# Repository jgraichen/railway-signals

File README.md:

# German model railway signals

<em lang="en">This repository contains 3d models, parts, and electronic components and boards to build german railway signals for H0 model railroading.</em>

## Signalkomponenten

- [Masten, Körbe, Zubehör](freecad/KS/Masten/README.md)
- [KS-Signalschirme](freecad/KS/Signalschirme/README.md)
  - [PCB für Hauptsignale](kicad/Hauptsignal/README.md)
  - [PCB für Mehrabschnittssignale](kicad/Mehrabschnittssignal/README.md)
  - [PCB für Vorsignale](kicad/Vorsignal/README.md)
- [Zusatzsignale](freecad/KS/Zusatzsignale/README.md)
  - [PCB für Zusatzsignale](kicad/Zusatzsignal/README.md)

## Zubehör

### Signal-Treiberplatinen

- [Adapterplatine für MGP Signaldekoder](kicad/extra/ws2811-adapter/README.md)
- [LED Treiberboard für ein wechselbares Lichtsperrsignal](kicad/extra/ws2811-driver-6ls/README.md)
- [LED Treiberboard für zwei wechselbare Lichtsperrsignale](kicad/extra/ws2811-driver-9ls/README.md)
- [12 LED Treiberboard (1 Signal)](kicad/extra/ws2811-driver-12/README.md)
- [24 LED Treiberboard (2 Signale)](kicad/extra/ws2811-driver-24/README.md)
- [Wattenscheider Schacht für LED Treiberboards](freecad/watti-signal-mount/README.md)

## License

See individual components. Otherwise, all components and parts are licensed under a [Creative Commons Attribution-ShareAlike 4.0 International License](http://creativecommons.org/licenses/by-sa/4.0/).

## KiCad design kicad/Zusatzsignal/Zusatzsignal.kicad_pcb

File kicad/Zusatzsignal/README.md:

# Zusatzsignal ZSv2

Geeignet für Zusatzsignale über oder unter dem Signalschirm.

## Anschlussbelegung

| Referenz | Pin | LED | Funktion            |
| -------- | --- | --- | ------------------- |
|          | +   |     | Stromversorgung (+) |
|          |     |     | Masse               |

## License

This work is licensed under a
[Creative Commons Attribution-ShareAlike 4.0 International License](http://creativecommons.org/licenses/by-sa/4.0/).

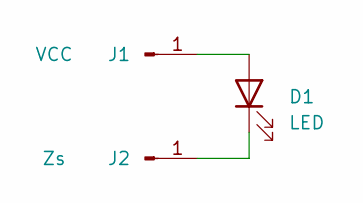
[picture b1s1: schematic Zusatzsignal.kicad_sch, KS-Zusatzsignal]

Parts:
D1: LED; LED_0603_1608Metric
J1: VCC; SolderWirePad_1x01_SMD_1x2mm
J2: Zs; SolderWirePad_1x01_SMD_1x2mm

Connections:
unnamed: D1.1 (K), J2.1
unnamed: D1.2 (A), J1.1

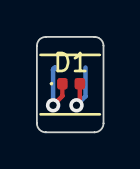
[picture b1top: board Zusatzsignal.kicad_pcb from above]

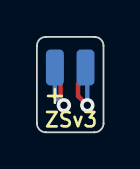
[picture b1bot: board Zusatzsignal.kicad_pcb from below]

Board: 2 copper layers, 3.7 x 5.3 mm, 3 parts (2 on the bottom side), 2 nets.

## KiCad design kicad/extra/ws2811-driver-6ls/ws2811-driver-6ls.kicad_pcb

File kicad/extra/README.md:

# Extra components

## WS2811 Adapter Board

An adapter boards to connect MGP signal decoders with driver boards via RJ45 cables, for longer distances and easier cabling.

Supports bypassing ports and looping back the digital signal to organize and optimize LED ordering. See the [board README](ws2811-adapter/README.md) for more details.

## WS2811 Driver 12 (1 Signal)

[LED driver board providing 12 LEDs](ws2811-driver-12/), intended for up to one fully equipped German KS signal. Can be mounted in a [Wattenscheider Schacht](../../freecad/watti-signal-mount/).

## WS2811 Driver 24 (2 Signals)

A [24 LED driver board](ws2811-driver-24/) for up to two fully equipped German KS signal, usually mounted on a signal gantry. Can be mounted in a [Wattenscheider Schacht](../../freecad/watti-signal-mount/).

## WS2811 Driver 6LS (1 LS)

This [driver board](ws2811-driver-6ls/) offers one tiny 2x3p 1 mm pitch connector for light shunting signals. The board can be mounted below the track, with the signal being mounted and connected through a 5 mm brass pole.

## WS2811 Driver 9LS (2 LS)

This [driver board](ws2811-driver-9ls/) offers two tiny 2x3p 1 mm pitch connectors for light shunting signals. The board can be mounted below the track, with the signal being mounted and connected through a 5 mm brass pole.

## License

See individual components. Otherwise, all components and parts are licensed under a [Creative Commons Attribution-ShareAlike 4.0 International License](http://creativecommons.org/licenses/by-sa/4.0/).

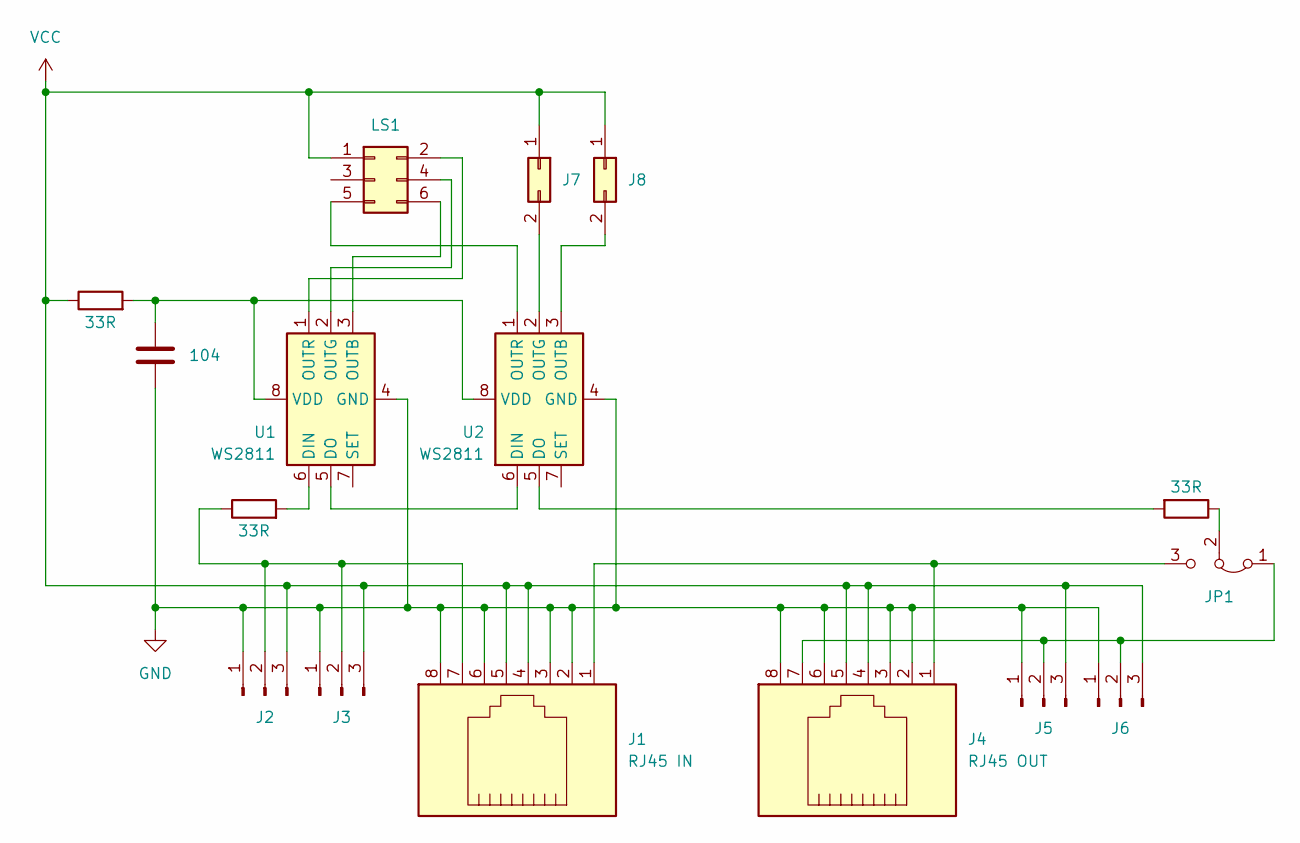
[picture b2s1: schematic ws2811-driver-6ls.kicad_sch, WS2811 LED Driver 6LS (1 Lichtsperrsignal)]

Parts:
C1: 104; C_0603_1608Metric; LCSC C14663
J1: RJ45 IN; RJ45_Amphenol_54602-x08_Horizontal
J2, J5: Conn_01x03_Pin; PinHeader_1x03_P2.54mm_Vertical
J3, J6: Conn_01x03_Pin; SolderWire-0.15sqmm_1x03_P4mm_D0.5mm_OD1.5mm_Relief
J4: RJ45 OUT; RJ45_Amphenol_54602-x08_Horizontal
J7, J8: Conn_02x01; PinHeader_2x01_P1.27mm_Vertical
JP1: Jumper_3_Bridged12; PinHeader_1x03_P2.54mm_Vertical
LS1: Conn_02x03_Odd_Even; PinHeader_2x03_P1.27mm_Vertical
R1, R2, R3: 33R; R_0603_1608Metric; LCSC C23140
U1, U2: WS2811; SOIC-8_3.9x4.9mm_P1.27mm; LCSC C114581

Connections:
GND: C1.2, J1.2, J1.3, J1.6, J1.8, J2.1, J3.1, J4.2, J4.3, J4.6, J4.8, J5.1, J6.1, U1.4 (GND), U2.4 (GND)
unnamed: J1.7, J2.2, J3.2, R2.1
unnamed: J4.7, J5.2, J6.2, JP1.1 (A)
unnamed: J7.2, U2.2 (OUTG)
unnamed: J8.2, U2.3 (OUTB)
unnamed: J1.1, J4.1, JP1.3 (B)
unnamed: JP1.2 (C), R3.1
unnamed: LS1.2, U1.1 (OUTR)
unnamed: LS1.4, U1.2 (OUTG)
unnamed: LS1.5, U2.1 (OUTR)
unnamed: LS1.6, U1.3 (OUTB)
unnamed: R2.2, U1.6 (DIN)
unnamed: U1.5 (DO), U2.6 (DIN)
unnamed: C1.1, R1.2, U1.8 (VDD), U2.8 (VDD)
unnamed: R3.2, U2.5 (DO)
VCC: J1.4, J1.5, J2.3, J3.3, J4.4, J4.5, J5.3, J6.3, J7.1, J8.1, LS1.1, R1.1

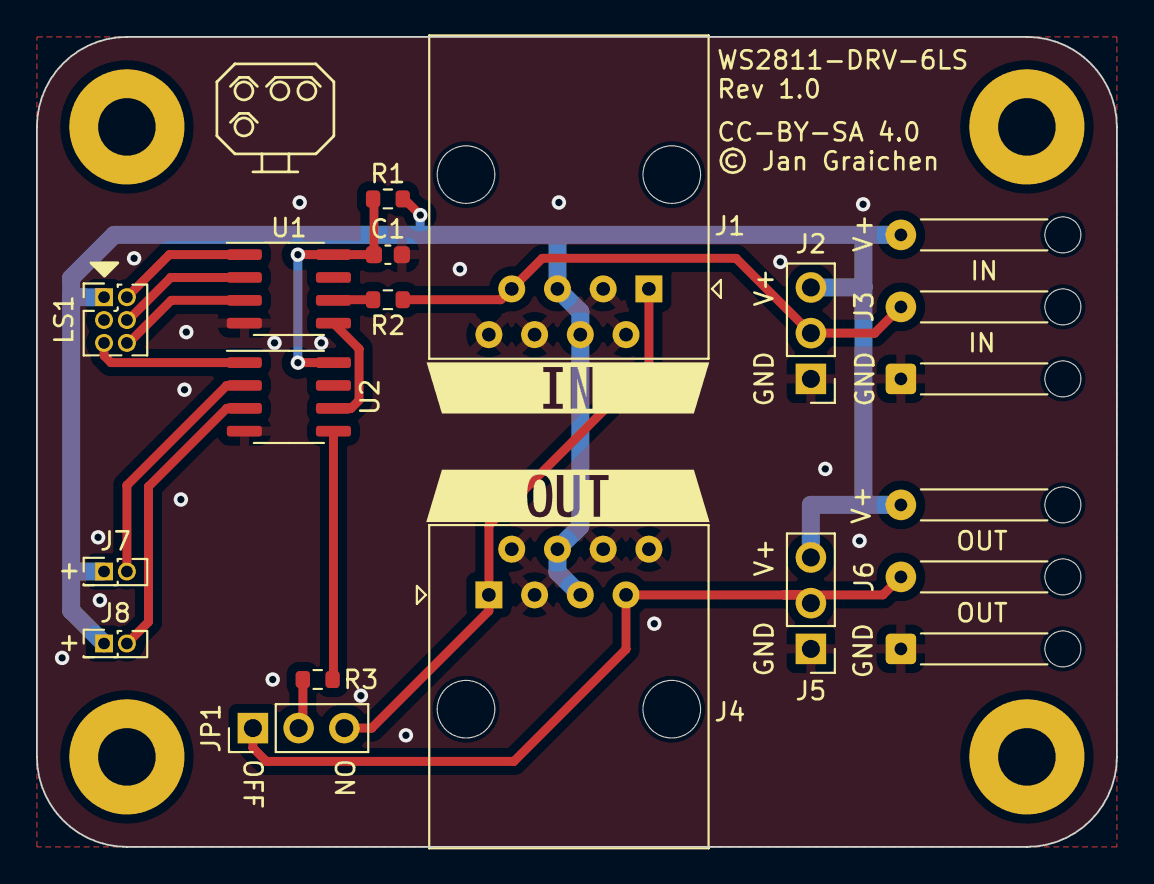
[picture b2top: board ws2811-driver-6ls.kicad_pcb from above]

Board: 2 copper layers, 60.0 x 45.0 mm, 18 parts (0 on the bottom side), 16 nets.

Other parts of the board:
kibuzzard-65AE6F8F: G***; kibuzzard-65AE6F8F
kibuzzard-65AE6F95: G***; kibuzzard-65AE6F95

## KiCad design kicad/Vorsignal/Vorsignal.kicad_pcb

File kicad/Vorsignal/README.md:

# Vorsignal

Geeignet für KS-Vorsignale.

## Anschlussbelegung

| Schema                | Pin-Belegung                    |
| --------------------- | ------------------------------- |
|  |  |

| Referenz | Pin | LED      | Funktion                   |
| -------- | --- | -------- | -------------------------- |
| J0       | +   |          | Stromversorgung (+)        |
| J1       | 1   | Kaltweiß | Verkürzter Bremswegabstand |
| J3       | 3   | Gelb     | Ks2 (Halt erwarten)        |
| J4       | 4   | Grün     | Ks1 (Fahrt erwarten)       |
| J9       | 9   | Kaltweiß | Wiederholer                |

## License

This work is licensed under a
[Creative Commons Attribution-ShareAlike 4.0 International License](http://creativecommons.org/licenses/by-sa/4.0/).

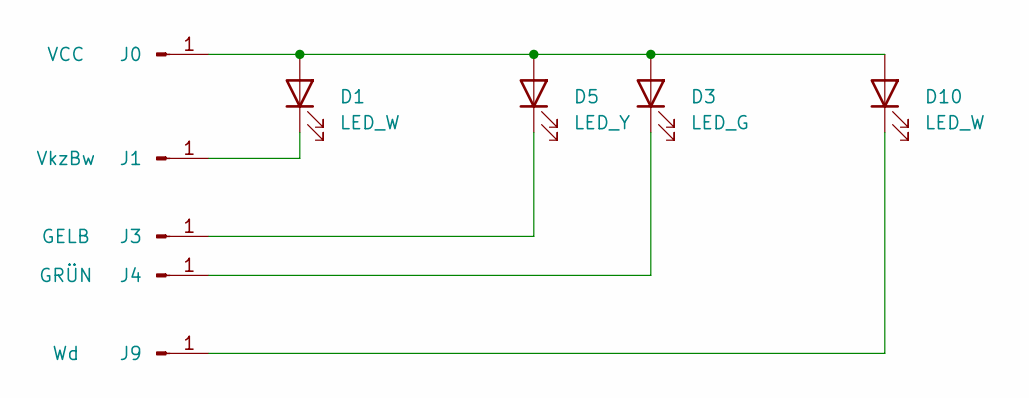
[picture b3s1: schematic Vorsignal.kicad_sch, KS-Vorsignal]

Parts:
D1, D10: LED_W; LED_0402_1005Metric; LCSC C189305
D3: LED_G; LED_0402_1005Metric; LCSC C409787
D5: LED_Y; LED_0402_1005Metric; LCSC C779450
J0: VCC; SolderWirePad_1x01_SMD_1x2mm
J1: VkzBw; SolderWirePad_1x01_SMD_1x2mm
J3: GELB; SolderWirePad_1x01_SMD_1x2mm
J4: GRÜN; SolderWirePad_1x01_SMD_1x2mm
J9: Wd; SolderWirePad_1x01_SMD_1x2mm

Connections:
unnamed: D1.2 (A), D3.2 (A), D5.2 (A), D10.2 (A), J0.1
unnamed: D1.1 (K), J1.1
unnamed: D3.1 (K), J4.1
unnamed: D5.1 (K), J3.1
unnamed: D10.1 (K), J9.1

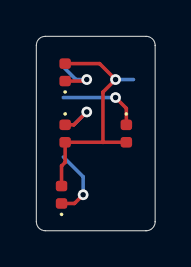
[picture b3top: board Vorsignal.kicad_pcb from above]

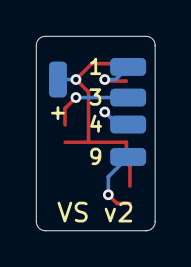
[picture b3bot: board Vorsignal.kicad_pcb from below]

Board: 2 copper layers, 6.6 x 10.8 mm, 9 parts (5 on the bottom side), 5 nets.

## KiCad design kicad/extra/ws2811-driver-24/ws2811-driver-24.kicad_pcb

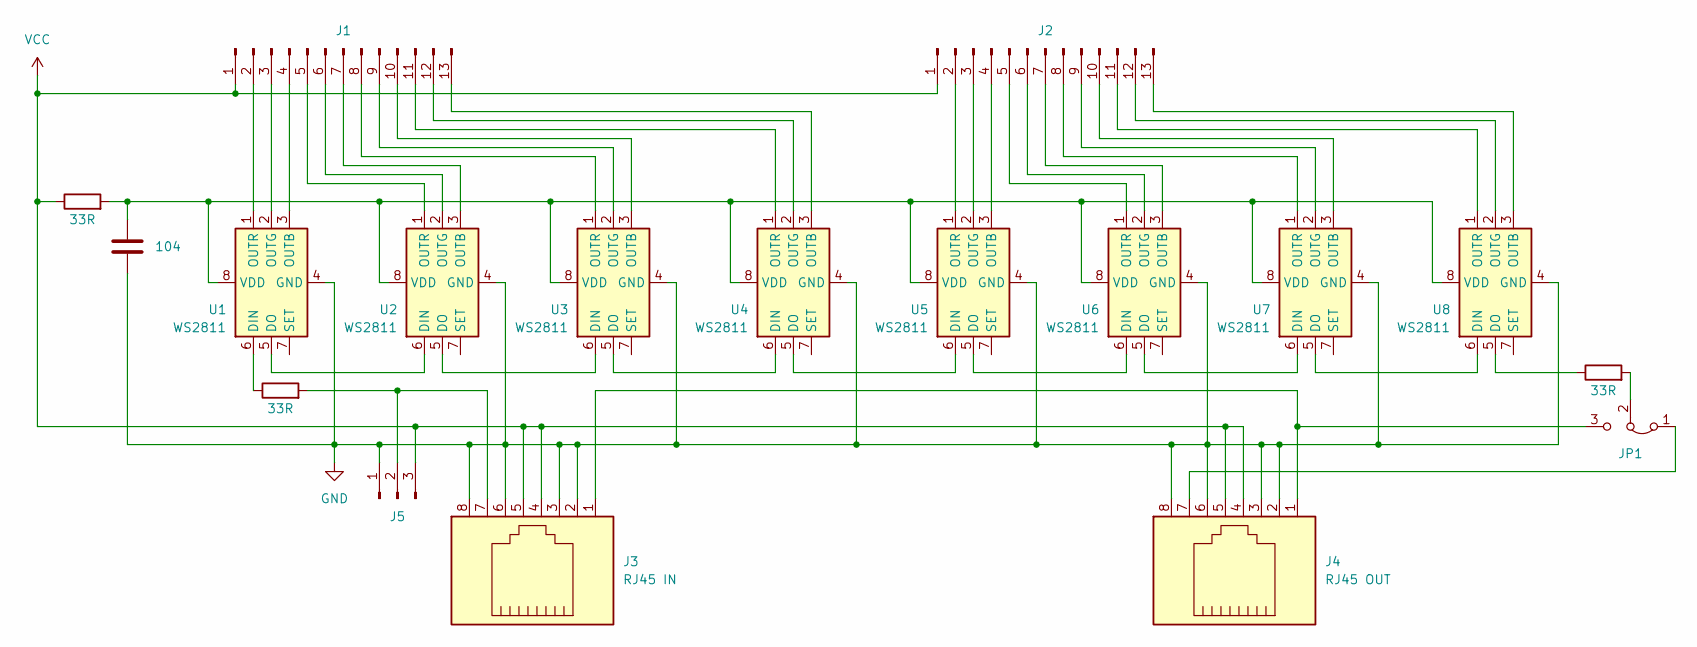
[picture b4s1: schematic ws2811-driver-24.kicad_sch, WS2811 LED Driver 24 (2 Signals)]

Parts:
C1: 104; C_0603_1608Metric
J1, J2: Conn_01x13_Pin; PinHeader_1x13_P2.54mm_Vertical
J3: RJ45 IN; RJ45_Amphenol_54602-x08_Horizontal
J4: RJ45 OUT; RJ45_Amphenol_54602-x08_Horizontal
J5: Conn_01x03_Pin; PinHeader_1x03_P2.54mm_Vertical
JP1: Jumper_3_Bridged12; PinHeader_1x03_P2.54mm_Vertical
R1, R2, R3: 33R; R_0603_1608Metric
U1, U2, U3, U4, U5, U6, U7, U8: WS2811; SOIC-8_3.9x4.9mm_P1.27mm

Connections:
GND: C1.2, J3.2, J3.3, J3.6, J3.8, J4.2, J4.3, J4.6, J4.8, J5.1, U1.4 (GND), U2.4 (GND), U3.4 (GND), U4.4 (GND), U5.4 (GND), U6.4 (GND), U7.4 (GND), U8.4 (GND)
unnamed: J1.2, U1.1 (OUTR)
unnamed: J1.3, U1.2 (OUTG)
unnamed: J1.4, U1.3 (OUTB)
unnamed: J1.5, U2.1 (OUTR)
unnamed: J1.6, U2.2 (OUTG)
unnamed: J1.7, U2.3 (OUTB)
unnamed: J1.8, U3.1 (OUTR)
unnamed: J1.9, U3.2 (OUTG)
unnamed: J1.10, U3.3 (OUTB)
unnamed: J1.11, U4.1 (OUTR)
unnamed: J1.12, U4.2 (OUTG)
unnamed: J1.13, U4.3 (OUTB)
unnamed: J2.2, U5.1 (OUTR)
unnamed: J2.3, U5.2 (OUTG)
unnamed: J2.4, U5.3 (OUTB)
unnamed: J2.5, U6.1 (OUTR)
unnamed: J2.6, U6.2 (OUTG)
unnamed: J2.7, U6.3 (OUTB)
unnamed: J2.8, U7.1 (OUTR)
unnamed: J2.9, U7.2 (OUTG)
unnamed: J2.10, U7.3 (OUTB)
unnamed: J2.11, U8.1 (OUTR)
unnamed: J2.12, U8.2 (OUTG)
unnamed: J2.13, U8.3 (OUTB)
unnamed: J3.7, J5.2, R2.2
unnamed: J4.7, JP1.1 (A)
unnamed: J3.1, J4.1, JP1.3 (B)
unnamed: JP1.2 (C), R3.2
unnamed: R2.1, U1.6 (DIN)
unnamed: U1.5 (DO), U2.6 (DIN)
unnamed: C1.1, R1.2, U1.8 (VDD), U2.8 (VDD), U3.8 (VDD), U4.8 (VDD), U5.8 (VDD), U6.8 (VDD), U7.8 (VDD), U8.8 (VDD)
unnamed: U2.5 (DO), U3.6 (DIN)
unnamed: U3.5 (DO), U4.6 (DIN)
unnamed: U4.5 (DO), U5.6 (DIN)
unnamed: U5.5 (DO), U6.6 (DIN)
unnamed: U6.5 (DO), U7.6 (DIN)
unnamed: U7.5 (DO), U8.6 (DIN)
unnamed: R3.1, U8.5 (DO)
VCC: J1.1, J2.1, J3.4, J3.5, J4.4, J4.5, J5.3, R1.1

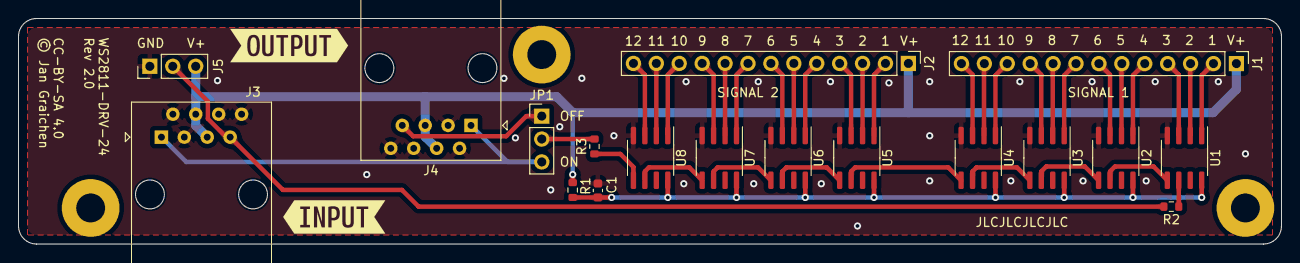
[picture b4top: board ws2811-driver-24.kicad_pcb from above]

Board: 2 copper layers, 140.0 x 25.0 mm, 20 parts (0 on the bottom side), 40 nets.

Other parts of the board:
kibuzzard-6563A51A: G***; kibuzzard-6563A51A
kibuzzard-6563A507: G***; kibuzzard-6563A507

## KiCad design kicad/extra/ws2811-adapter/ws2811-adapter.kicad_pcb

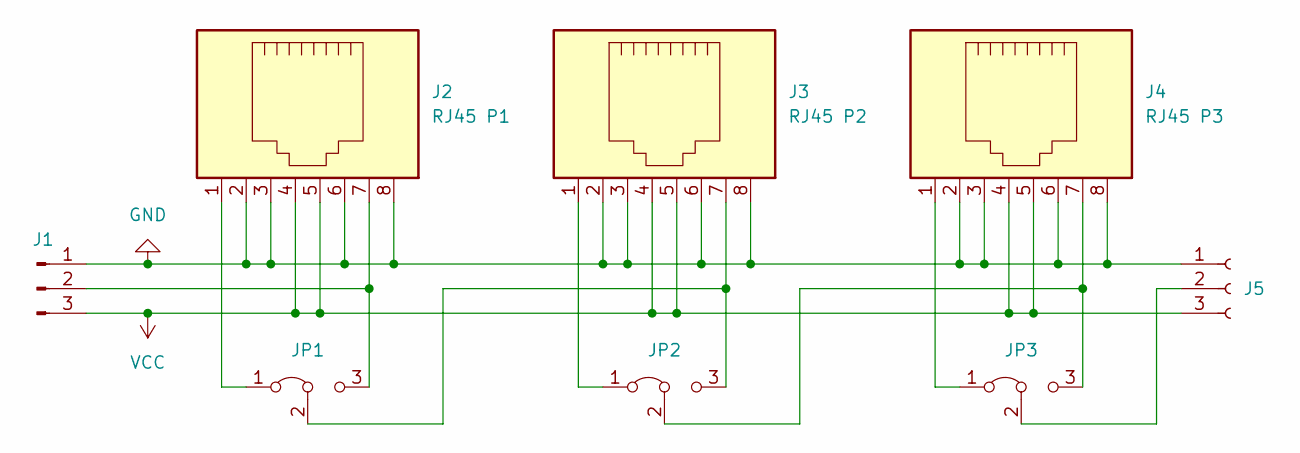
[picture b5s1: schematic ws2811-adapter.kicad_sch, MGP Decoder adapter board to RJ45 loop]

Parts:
J1: Conn_01x03_Pin; PinHeader_1x03_P2.54mm_Vertical
J2: RJ45 P1; RJ45_Amphenol_54602-x08_Horizontal
J3: RJ45 P2; RJ45_Amphenol_54602-x08_Horizontal
J4: RJ45 P3; RJ45_Amphenol_54602-x08_Horizontal
J5: Conn_01x03_Socket; PinSocket_1x03_P2.54mm_Vertical
JP1, JP2, JP3: Jumper_3_Bridged12; PinHeader_1x03_P2.54mm_Vertical

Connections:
GND: J1.1, J2.2, J2.3, J2.6, J2.8, J3.2, J3.3, J3.6, J3.8, J4.2, J4.3, J4.6, J4.8, J5.1
unnamed: J1.2, J2.7, JP1.3 (B)
unnamed: J5.2, JP3.2 (C)
unnamed: J2.1, JP1.1 (A)
unnamed: J3.7, JP1.2 (C), JP2.3 (B)
unnamed: J3.1, JP2.1 (A)
unnamed: J4.7, JP2.2 (C), JP3.3 (B)
unnamed: J4.1, JP3.1 (A)
VCC: J1.3, J2.4, J2.5, J3.4, J3.5, J4.4, J4.5, J5.3

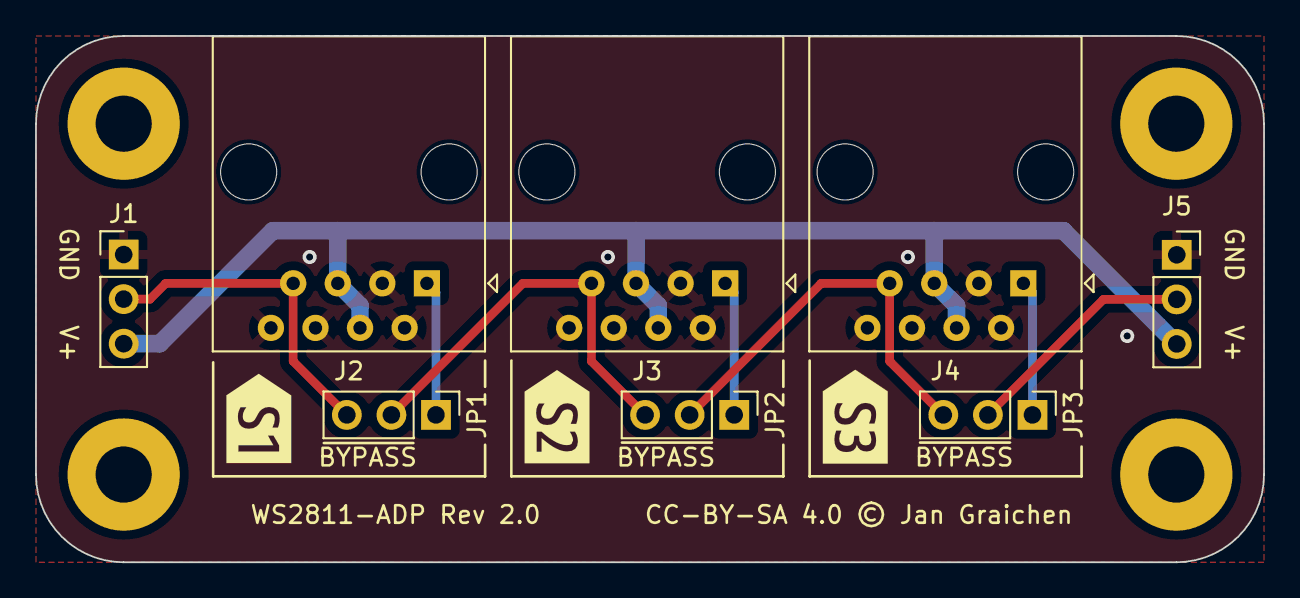
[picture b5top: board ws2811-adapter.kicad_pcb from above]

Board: 2 copper layers, 70.0 x 30.0 mm, 11 parts (0 on the bottom side), 9 nets.

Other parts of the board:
kibuzzard-6563BF6D: G***; kibuzzard-6563BF6D
kibuzzard-6563BF62: G***; kibuzzard-6563BF62
kibuzzard-6563BF69: G***; kibuzzard-6563BF69

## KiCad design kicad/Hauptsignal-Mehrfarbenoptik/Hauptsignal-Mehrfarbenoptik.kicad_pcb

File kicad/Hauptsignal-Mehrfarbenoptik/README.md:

# Hauptsignal mit mehrfarbiger Optik MSOv1

Geeignet für KS-Hauptsignale und Mehrabschnitssignale mit mehrfarbiger Optik über eine ARGB-LED.

Pin 1 muss die gemeinsame Anode der RGB LED sein, die anderen Pins können je nach Bedarf Rot, Grün, oder Blau sein. Das ermöglicht auch den Einsatz auch von zum Beispiel ARGB und ARBG LEDs.

## Anschlussbelegung

| Schema                | Pin-Belegung                    |
| --------------------- | ------------------------------- |
|  |  |

| Referenz | Pin | LED      | Funktion                         |
| -------- | --- | -------- | -------------------------------- |
| J0       | +   |          | Stromversorgung (+)              |
| J1       | 1   | Kaltweiß | Zusatzlicht (oben)               |
| J2       | 2   | ARGB_2   | RGB Led Pin 2                    |
| J3       | 3   | ARGB_3   | RGB Led Pin 3                    |
| J4       | 4   | ARGB_4   | RGB Led Pin 4                    |
| J5       | 5   | Gelb     | Zs7                              |
| J6       | 6   | Kaltweiß | Sh1/Ra12                         |
| J7       | 7   | Gelb     | Zs7                              |
| J8       | 8   | Gelb     | Zs7                              |
| J9       | 9   | Kaltweiß | Sh1/Ra12/Zs1/Zusatzlicht (unten) |

## License

This work is licensed under a
[Creative Commons Attribution-ShareAlike 4.0 International License](http://creativecommons.org/licenses/by-sa/4.0/).

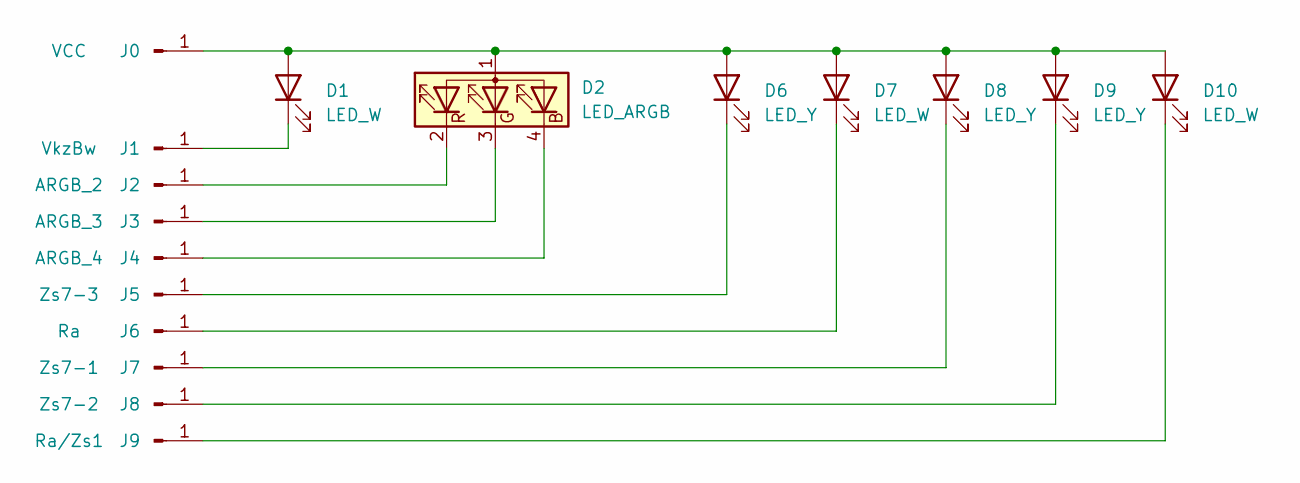
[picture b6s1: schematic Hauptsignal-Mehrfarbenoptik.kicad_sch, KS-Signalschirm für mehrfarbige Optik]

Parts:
D1, D7, D10: LED_W; LED_0402_1005Metric
D2: LED_ARGB; LRTBR48GP9Q71R7S526NP68
D6, D8, D9: LED_Y; LED_0402_1005Metric
J0: VCC; SolderWirePad_1x01_SMD_1x2mm
J1: VkzBw; SolderWirePad_1x01_SMD_1x2mm
J2: ARGB_2; SolderWirePad_1x01_SMD_1x2mm
J3: ARGB_3; SolderWirePad_1x01_SMD_1x2mm
J4: ARGB_4; SolderWirePad_1x01_SMD_1x2mm
J5: Zs7-3; SolderWirePad_1x01_SMD_1x2mm
J6: Ra; SolderWirePad_1x01_SMD_1x2mm
J7: Zs7-1; SolderWirePad_1x01_SMD_1x2mm
J8: Zs7-2; SolderWirePad_1x01_SMD_1x2mm
J9: Ra/Zs1; SolderWirePad_1x01_SMD_1x2mm

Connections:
unnamed: D1.1 (K), J1.1
unnamed: D1.2 (A), D2.1 (A), D6.2 (A), D7.2 (A), D8.2 (A), D9.2 (A), D10.2 (A), J0.1
unnamed: D2.2 (RK), J2.1
unnamed: D2.3 (GK), J3.1
unnamed: D2.4 (BK), J4.1
unnamed: D6.1 (K), J5.1
unnamed: D7.1 (K), J6.1
unnamed: D8.1 (K), J7.1
unnamed: D9.1 (K), J8.1
unnamed: D10.1 (K), J9.1

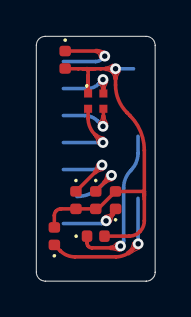
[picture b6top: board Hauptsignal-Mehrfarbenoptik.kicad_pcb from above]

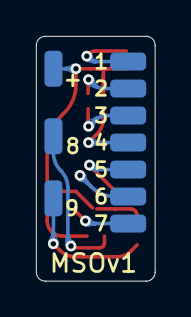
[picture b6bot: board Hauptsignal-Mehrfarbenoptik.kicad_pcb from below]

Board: 2 copper layers, 6.6 x 13.6 mm, 17 parts (10 on the bottom side), 10 nets.

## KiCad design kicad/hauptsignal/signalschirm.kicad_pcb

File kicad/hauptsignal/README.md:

# Hauptsignal/Mehrabschnittssignal

Geeignet für Hauptsignale und Mehrabschnittssignale.

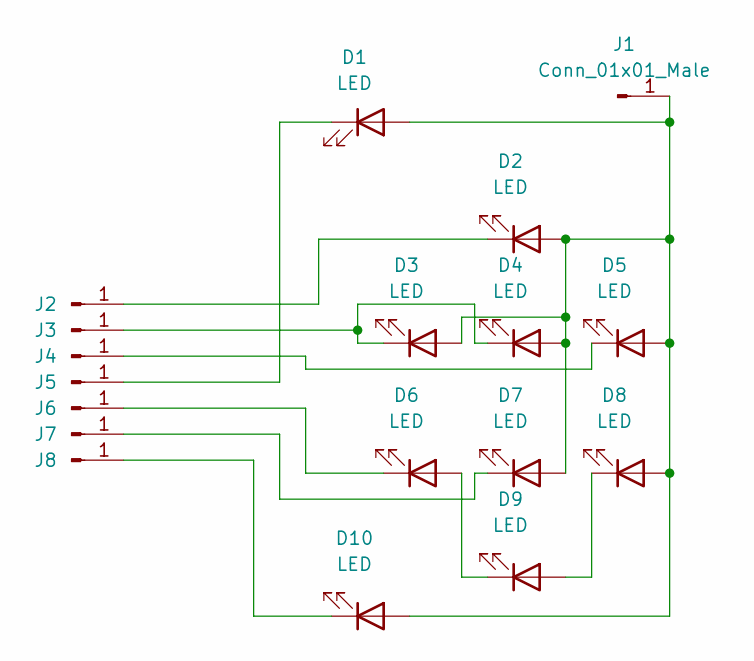
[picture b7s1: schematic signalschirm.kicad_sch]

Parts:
D1, D2, D3, D4, D5, D6, D7, D8, D9, D10: LED; LED_0402_1005Metric
J1, J2, J3, J4, J5, J6, J7, J8: Conn_01x01_Male; SolderWirePad_1x01_SMD_1x2mm

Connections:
unnamed: D1.1 (K), J5.1
unnamed: D2.1 (K), J2.1
unnamed: D1.2 (A), D2.2 (A), D3.2 (A), D4.2 (A), D5.2 (A), D7.2 (A), D8.2 (A), D10.2 (A), J1.1
unnamed: D3.1 (K), D4.1 (K), J3.1
unnamed: D5.1 (K), J4.1
unnamed: D6.1 (K), J6.1
unnamed: D6.2 (A), D9.1 (K)
unnamed: D7.1 (K), J7.1
unnamed: D8.1 (K), D9.2 (A)
unnamed: D10.1 (K), J8.1

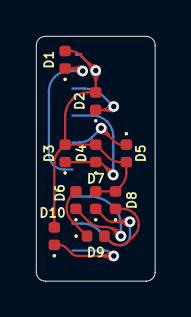
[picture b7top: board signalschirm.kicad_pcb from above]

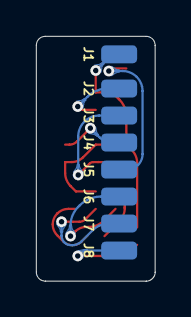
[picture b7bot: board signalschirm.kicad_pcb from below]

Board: 2 copper layers, 6.6 x 13.6 mm, 18 parts (8 on the bottom side), 10 nets.

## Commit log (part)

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2022-11-12 Füge Pfeiler hinzu
    Signal Pfeiler
    Parametrisiert: Höhe, Länge der Stütze, Höhe des Seitenteils
2022-11-12 Add README
2022-11-12 Add PCB for Zs with 2 LEDs
2022-11-13 Add PCB for main signals
    The PCB supports main signals and multi block signals. Unnecessary LEDs
    do not need to be populated. A green LED can be placed in the middle for
    main signals, and left for multi block signals.
    Other LED footprints support Zs1, Zs7, Sh1, Kennlicht, and the shortened
    breaking distance indicator.
2022-11-13 Shrink PCB element size and add rounded tracks and teardrops
2022-12-18 MSv2
2022-12-18 Add HSv1 KS-Hauptsignalschirm
2022-12-18 Update docs
2022-12-18 Update MS README
2022-12-18 Update HS readme
2022-12-18 Update front
2022-12-18 Update ZS readme
2022-12-19 feat: Add untested multi-color signal front
2022-12-19 fix: Remove useless wire trace left from MSv2
2022-12-19 feat: Script to generate pcbdraw previews
2022-12-20 feat: re-route MSO
2022-12-20 fix: MSO missing trace
2022-12-20 MS: try using JLCPCB parts from library
    Assign some LEDs available in JLCPCB's inhouse catalog.
2022-12-20 fix: Avoid useless output when generating previews
2022-12-23 Uwe testet git
2022-12-28 fix: spelling in README
2023-01-15 MS: keep more space to border for breakout
2023-01-15 Add panelization rule presets
    Optimized for own panelization for JLCPCB rules
2023-10-31 feat: Change ZS to use 0403 LED
    Try production step with same LEDs as used on the main signals.
2023-10-31 feat: Update all panel code
    Generate panels with full local config for reproducability into a
    sub-directory, for example:
    kikit panelize -p panel.json Mehrabschnittssignal.kicad_pcb panel/MSv2-panel.kicad_pcb
2023-10-31 chore: regenerate preview
2023-11-05 feat: Add Vorsignal
2023-11-05 fix: Change panel size to minimal size needed for vcut
    Let's produce as less as possible signals but as many as needed not to
    waste space that is needed. The panel size must be at least 70x70mm so
    that the panel can be v-cutted.
2023-11-06 fix: ZS PCBs are to small for JLCPCB panelization
    JLCPCB only produces panelized boards with a minimum board size of
    5x5mm. Therefore, we must generate a mousebite "panel" and order that as
    "not-a-panel".
2023-11-18 Update LCSC part numbers in schema
2023-12-04 Add renovate.json
2023-12-09 feat: Add signal mount LED driver boards
2023-12-09 feat: Add 3D printables for signal mounts
2023-12-10 fix: LED ids
2023-12-14 Configure solder mask and silkscreen color
    Configure the default colors in board configuration for the current white finish.
2023-12-17 Add CC-BY-SA 4.0 license
2023-12-17 Add mian README as introducation
2023-12-22 feat: Rework WS2811 boards (Rev 2.0)
    * Change RJ45 pinout: The data signal is always paired with a ground
    line to increase signal stability, and the changed wireing eases the
    traces on the boards.
    * All WS2811 driver boards have a three pin header for direct drive now.
    They can be directly connected to a signal decoder, e.g. for testing.
    * The adapter boards has jumper pins to bypass RJ45 jacks, in case you
2024-01-01 extra: Add schema PDFs for MGP adapter boards
2024-01-01 chore: Add diff processor for FreeCAD files
    See
    https://wiki.freecad.org/WebTools_Git#Enabling_human-readable_diffs_for_FCStd_files_with_the_fcinfo_utility.
2024-01-13 feat: Add cover plate for Watti
    For now, only for the Watti with latch assembly.
2024-01-13 feat(VS): Add pre-signal repeater light
2024-01-23 feat: Add driver boards for KS Ls groups
    Two board variants for connecting one or two German light shunting signals
    via 2x3P 1mm pitch connectors.
2024-01-25 feat(models): Add MS and VS signal screens
2024-01-25 chore: Adjust preview sizes in readme
2024-01-25 feat(model): Erste Zusatzsignale Zs3/Zs3v 40 und Zs6
2024-01-26 feat: Reorganize exports and add STEP export
2024-01-26 feat: Add Makefile and schema export to boards
2024-01-26 feat: Start working on signal posts
2024-01-26 fix: Step export links for pre signals
2024-01-26 feat: Auslegermast 60/40 1ZS
2024-01-26 fix: Combined parts should not have mounting holes
2024-01-26 chore: Update parts
2024-01-27 feat: Optimize KS signal poles
    1. Remove mounts for signal pole sign. Instead, the same mounting holes
    as for the ladder are on both sides. I'll add a 3D printable pole
    sign mount next. This makes to the pole symmetrical too, so it can be
    used for left and right positions, if printed without the top pole
    segment.
    2. Add position pins for printing the signal pole in two or three
2024-01-28 feat!: Do not export step by default anymore
2024-01-28 feat: Add new 40/60/80 beam poles, pole signals
    * Also includes parts for either pre-print or post-print assembly.
2024-01-28 feat: Build post-print assemply poles from shared parts too
    1. The signal posts for post-print assembly are using the same base
    model parts now as the pre-post assembly poles, and are available in
    all three sizes too.
    2. Fix the inner pole pocket to 2.6mm for mounting a 2.5mm brass pole
    for all signal poles now.
2024-01-28 feat: Add signal pole ladders
2024-01-28 fix: Ausleger 2ZS
2024-01-28 feat: Add yellow tech mushroom
2024-01-30 chore: Update README for light shunting signals
2024-01-30 chore: Add README for extra driver board overview
2024-01-30 chore: Update ws2811-adapter preview images
2024-01-30 chore: fix image in extra README
2024-02-02 feat: diffusors for ZS
2024-02-02 feat: Mastschilder
2024-02-04 feat: Add ZS mount
2024-02-05 feat: Thicker ladders for easier printing
2024-02-15 Workaround running scripts in FreeCAD
2024-02-15 fix: Zs6 sizing
2024-02-15 feat: Add Zs3v plate
2024-02-15 Fix: ZS fest
2024-03-03 feat: KS Ausleger Mastkorb
2024-03-24 chore: Reorganize main signal models
    * Consistent naming
    * Generate README preview from available files
    * Export STEP files for higher precision exports
2024-03-24 chore: Generate new README for ZS
2024-03-24 chore: Update READMEs
2024-03-24 feat: Add pole overview and README
2024-03-24 chore: Generate missing step model exports
2024-03-24 Update exports
2024-03-29 fix: links to LS boards in README
2024-05-24 WIP: Redesign masts for single component production
2024-05-24 feat: Add signal mast basement
2024-05-24 feat: Prepare new mast generation
    Mast changes:
    1) All masts will be printable a single mast components,
    2) added edges and walls for pushing cables through the part,
    3) increased stability with lattice mast parts.
    Technical improvements:
    1) New mast assembly will use FreeCAD 0.22dev builtin assembly
2024-05-25 fix: Restore original export.py script
    Note: this does not work for STEP export of new assemblies
2024-05-25 feat: Auslegermast 48/40/Links
2024-05-25 feat: Add default CC-BY-SA 4.0 license text
2024-06-10 chore(deps): lock file maintenance
2025-05-05 chore(deps): update python to ==3.13.*
2025-05-06 chore: Bootstrap documentation
2025-05-12 chore(deps): update astral-sh/setup-uv action to v6
2025-05-12 fix(deps): update dependency mkdocs-material to ~=9.6.13
2025-08-18 chore(deps): update actions/checkout action to v5
2025-08-25 chore(deps): update actions/upload-pages-artifact action to v4
2025-09-08 chore(deps): update actions/setup-python action to v6
2025-09-21 fix(deps): update dependency mkdocs-awesome-nav to ~=3.2.0
2025-10-13 chore(deps): update astral-sh/setup-uv action to v7
2025-10-13 chore(deps): update python docker tag
2025-11-17 fix(deps): update dependency mkdocs-material to ~=9.7.0
2025-11-24 chore(deps): update actions/checkout action to v6
2025-12-08 fix(deps): update dependency mkdocs-awesome-nav to ~=3.3.0
2026-01-25 freecad: Adapt export script to support FC 1+ assemblies
2026-01-25 KS: Add MS Zs7+Sh1
2026-01-25 KS: Rework Gittermast for better stability
2026-01-25 KS: Add Gittermast 1ZS
2026-01-25 KS: Add new ZS "P" and "2"
2026-01-25 KS: Update image exports
2026-01-25 KS: Regenerate aux readme
2026-01-25 KS/ZS: Update README
2026-01-25 KS/ZS: Add Zs3 30 km/h
2026-03-30 chore(deps): update actions/configure-pages action to v6
2026-03-30 chore(deps): pin dependencies
2026-04-06 chore(deps): update actions/deploy-pages action to v5
2026-04-20 chore(deps): update actions/upload-pages-artifact action to v5
2026-04-27 chore(deps): update astral-sh/setup-uv action to v8
2026-06-19 chore(deps): update astral-sh/setup-uv action to v8.2.0
2026-06-19 chore(deps): update actions/checkout digest to df4cb1c
2026-06-22 chore(deps): update actions/checkout action to v7
2026-06-29 chore(deps): update actions/setup-python digest to ece7cb0

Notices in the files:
kicad/extra/ws2811-adapter/ws2811-adapter.kicad_pcb:
CC-BY-SA 4.0 © Jan Graichen
kicad/extra/ws2811-driver-6ls/ws2811-driver-6ls.kicad_sch:
© CC-BY-SA 4.0
